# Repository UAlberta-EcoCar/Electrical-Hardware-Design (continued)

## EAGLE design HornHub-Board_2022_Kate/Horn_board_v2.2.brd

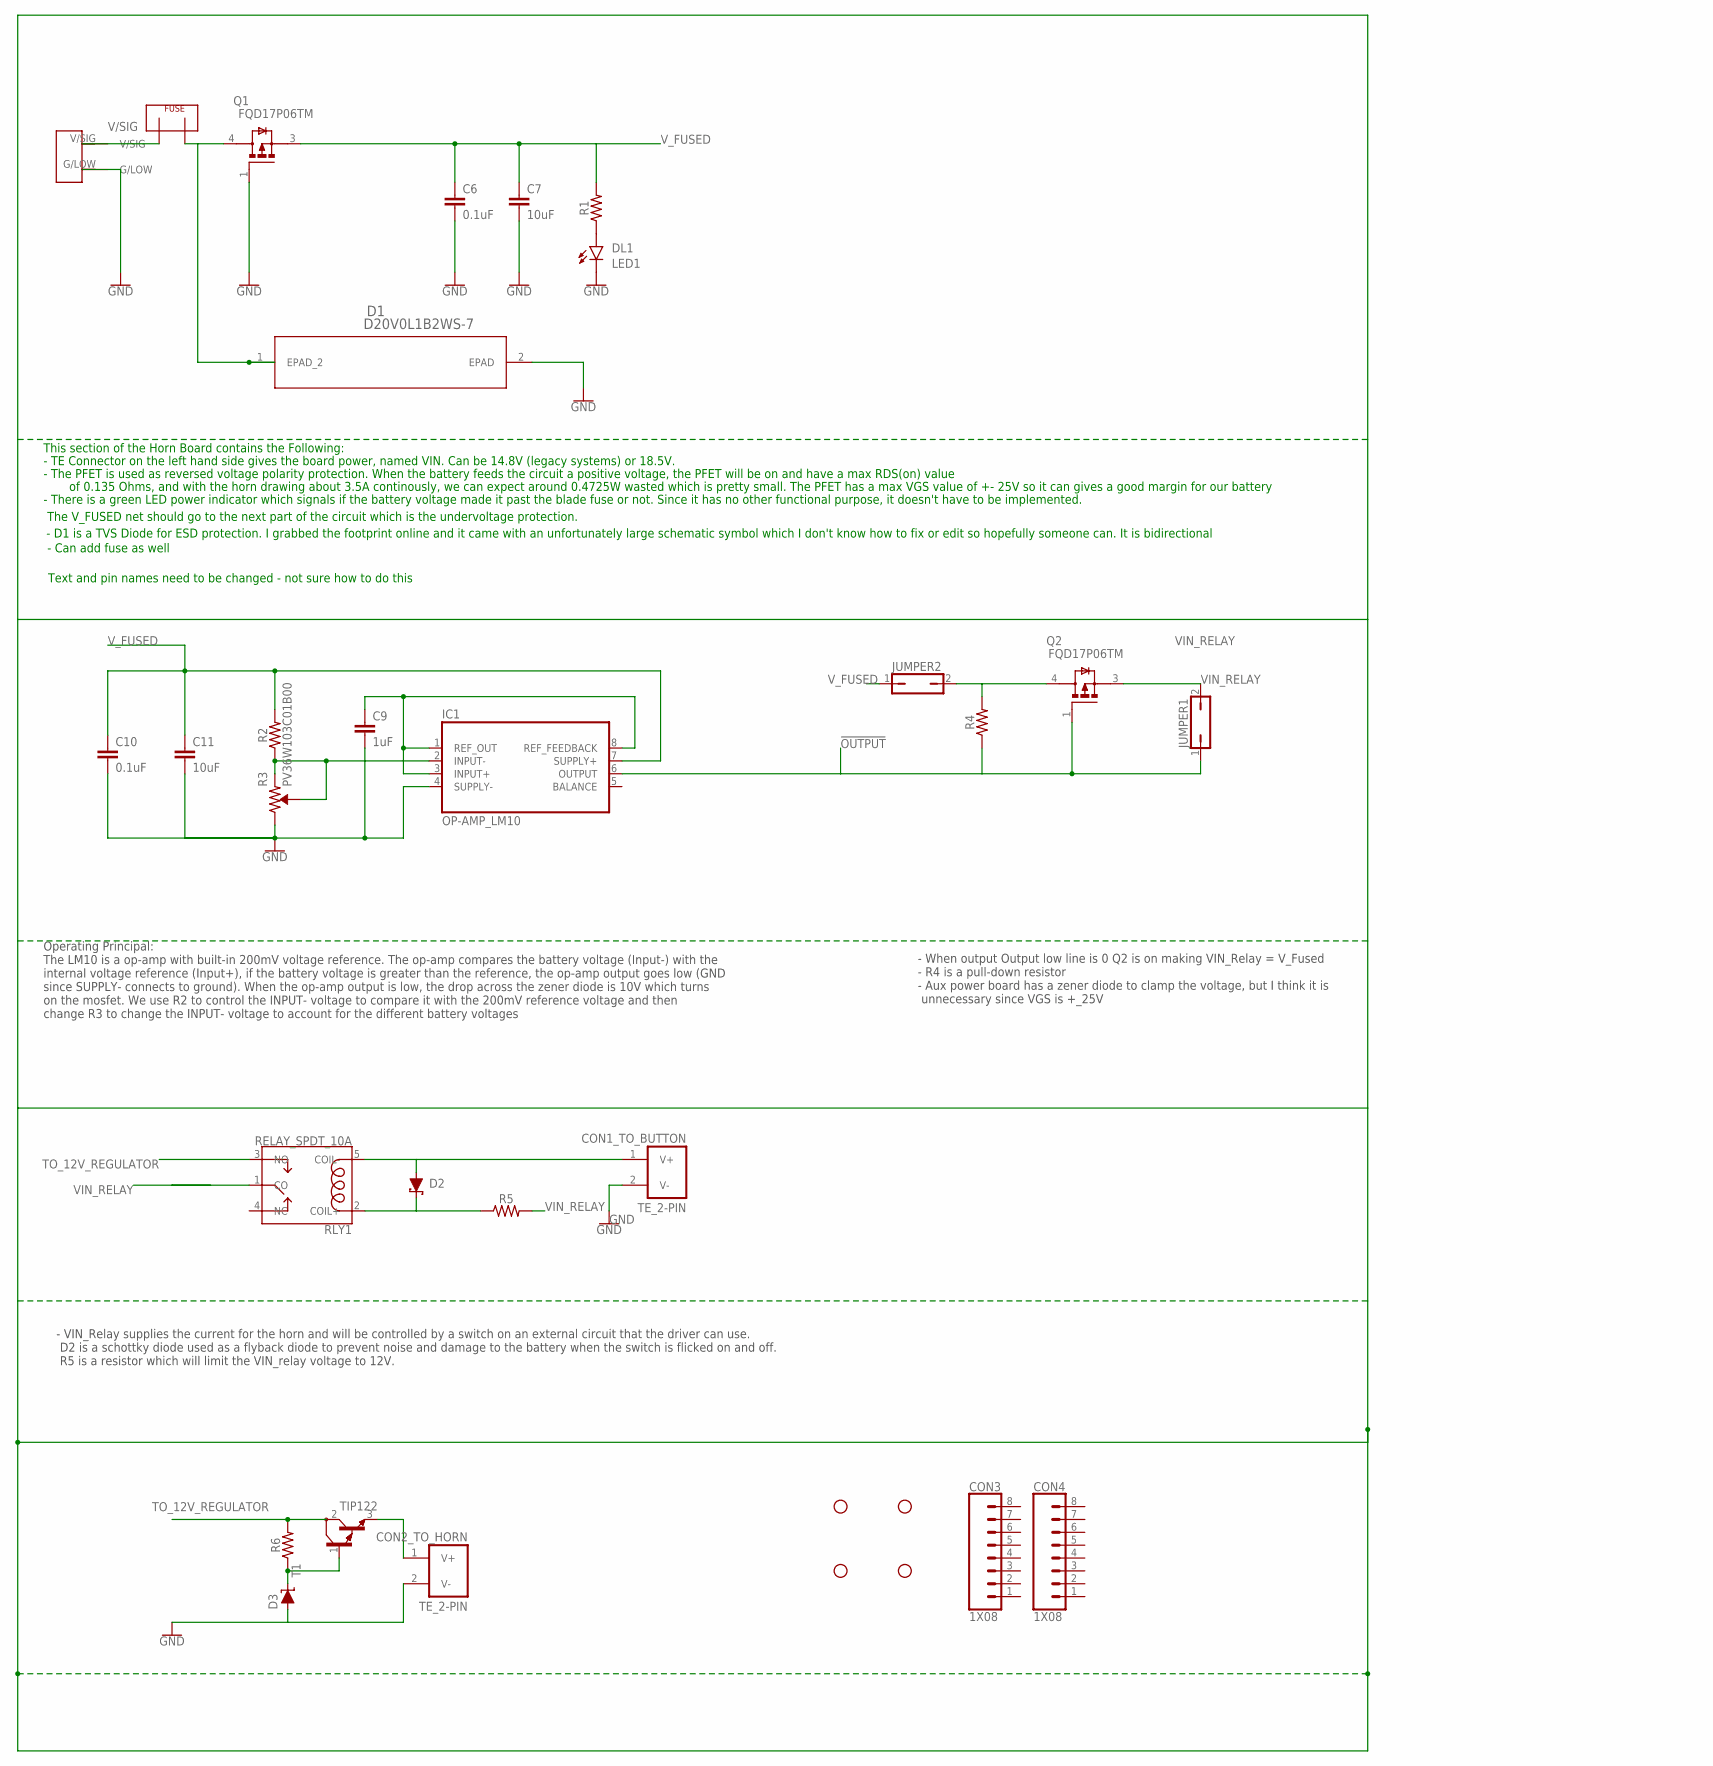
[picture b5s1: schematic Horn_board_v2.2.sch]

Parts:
C6, C10: 0.1uF; 1210
C7, C11: 10uF; 1210
C9: 1uF; 1210
CON1_TO_BUTTON, CON2_TO_HORN: TE_2-PIN
CON3, CON4: 1X08
D1: D20V0L1B2WS-7; SOD323_DIO
D2: DIODE_SCHOTTKY_DO-214AA; DO214AA
D3: DIODE_TVS_DO-214AA; DO214AA
F1: FUSEMINI-BLADE; MINI-BLADE-FUSE
H1, H2, H3, H4: STAND-OFF
IC1: OP-AMP_LM10; DIP08
JUMPER1, JUMPER2: JP1Q; JP1
LED1: DL1; 0805_LED
PWR: 2_PIN_TECONNECTOR; 2_PIN_CONNECT
Q1, Q2: FQD17P06TM; DPAK229P990X239-4N
R1, R2, R4, R5, R6: RESISTOR_1210; 1210
R3: PV36W103C01B00; TRIMPOT
RLY1: RELAY_SPDT_10A
T1: TIP122; TO220

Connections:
!OUTPUT: IC1.6 (OUTPUT), JUMPER1.1, Q2.1 (G), R4.1
GND: C6.2, C7.2, C10.2, C11.2, CON1_TO_BUTTON.2 (V-), CON2_TO_HORN.2 (V-), D1.2 (EPAD), D3.A, LED1.2 (C), PWR.G/LOW, Q1.1 (G), R3.3 (CW)
unnamed: C9.2, IC1.4 (SUPPLY-)
unnamed: LED1.1 (A), R1.1
unnamed: IC1.2 (INPUT-), R2.1, R3.1 (CCW), R3.2 (WIPER)
unnamed: C9.1, IC1.1 (REF_OUT), IC1.3 (INPUT+), IC1.8 (REF_FEEDBACK)
unnamed: JUMPER2.2, Q2.4 (D), R4.2
unnamed: D2.C, R5.1, RLY1.2 (COIL+)
unnamed: CON1_TO_BUTTON.1 (V+), D2.A, RLY1.5 (COIL-)
unnamed: D3.C, R6.1, T1.1 (B)
unnamed: CON2_TO_HORN.1 (V+), T1.3 (E)
TO_12V_REGULATOR: R6.2, RLY1.3 (NO), T1.2 (C)
V/SIG: F1.OUT, PWR.V/SIG
VIN: D1.1 (EPAD_2), F1.IN, Q1.4 (D)
VIN_RELAY: JUMPER1.2, Q2.3 (S), R5.2
V_FUSED: C6.1, C7.1, C10.1, C11.1, IC1.7 (SUPPLY+), JUMPER2.1, Q1.3 (S), R1.2, R2.2

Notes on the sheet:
This section of the Horn Board contains the Following:
- TE Connector on the left hand side gives the board power, named VIN. Can be 14.8V (legacy systems) or 18.5V.
- The PFET is used as reversed voltage polarity protection. When the battery feeds the circuit a positive voltage, the PFET will be on and have a max RDS(on) value
- There is a green LED power indicator which signals if the battery voltage made it past the blade fuse or not. Since it has no other functional purpose, it doesn't have to be implemented.
of 0.135 Ohms, and with the horn drawing about 3.5A continously, we can expect around 0.4725W wasted which is pretty small. The PFET has a max VGS value of +- 25V so it can gives a good margin for our battery
The V_FUSED net should go to the next part of the circuit which is the undervoltage protection.
- D1 is a TVS Diode for ESD protection. I grabbed the footprint online and it came with an unfortunately large schematic symbol which I don't know how to fix or edit so hopefully someone can. It is bidirectional
Text and pin names need to be changed - not sure how to do this
- Can add fuse as well
Operating Principal: The LM10 is a op-amp with built-in 200mV voltage reference. The op-amp compares the battery voltage (Input-) with the internal voltage reference (Input+), if the battery voltage is greater than the reference, the op-amp output goes low (GND since SUPPLY- connects to ground). Wh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
- When output Output low line is 0 Q2 is on making VIN_Relay = V_Fused - R4 is a pull-down resistor - Aux power board has a zener diode to clamp the voltage, but I think it is unnecessary since VGS is +_25V
- VIN_Relay supplies the current for the horn and will be controlled by a switch on an external circuit that the driver can use. D2 is a schottky diode used as a flyback diode to prevent noise and damage to the battery when the switch is flicked on and off. R5 is a resistor which will limit the VIN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

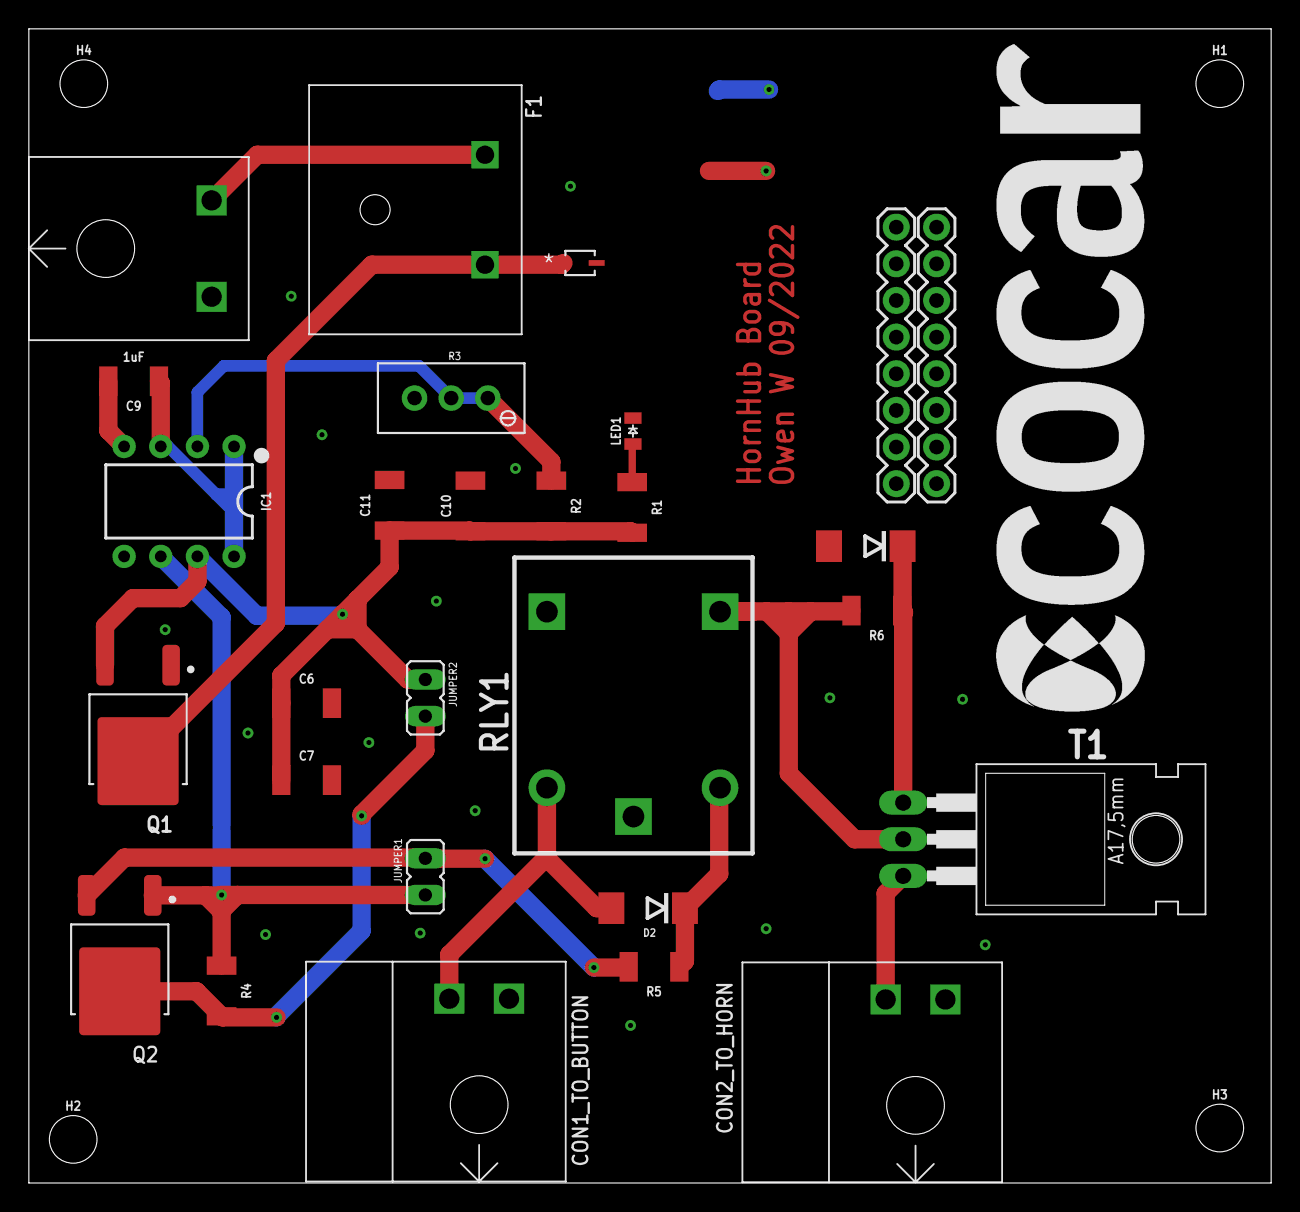
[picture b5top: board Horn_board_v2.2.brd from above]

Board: 2 copper layers, 86.1 x 80.0 mm, 33 parts (0 on the bottom side), 16 nets.

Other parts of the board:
U$1: ECOCAR_LOGO_2018

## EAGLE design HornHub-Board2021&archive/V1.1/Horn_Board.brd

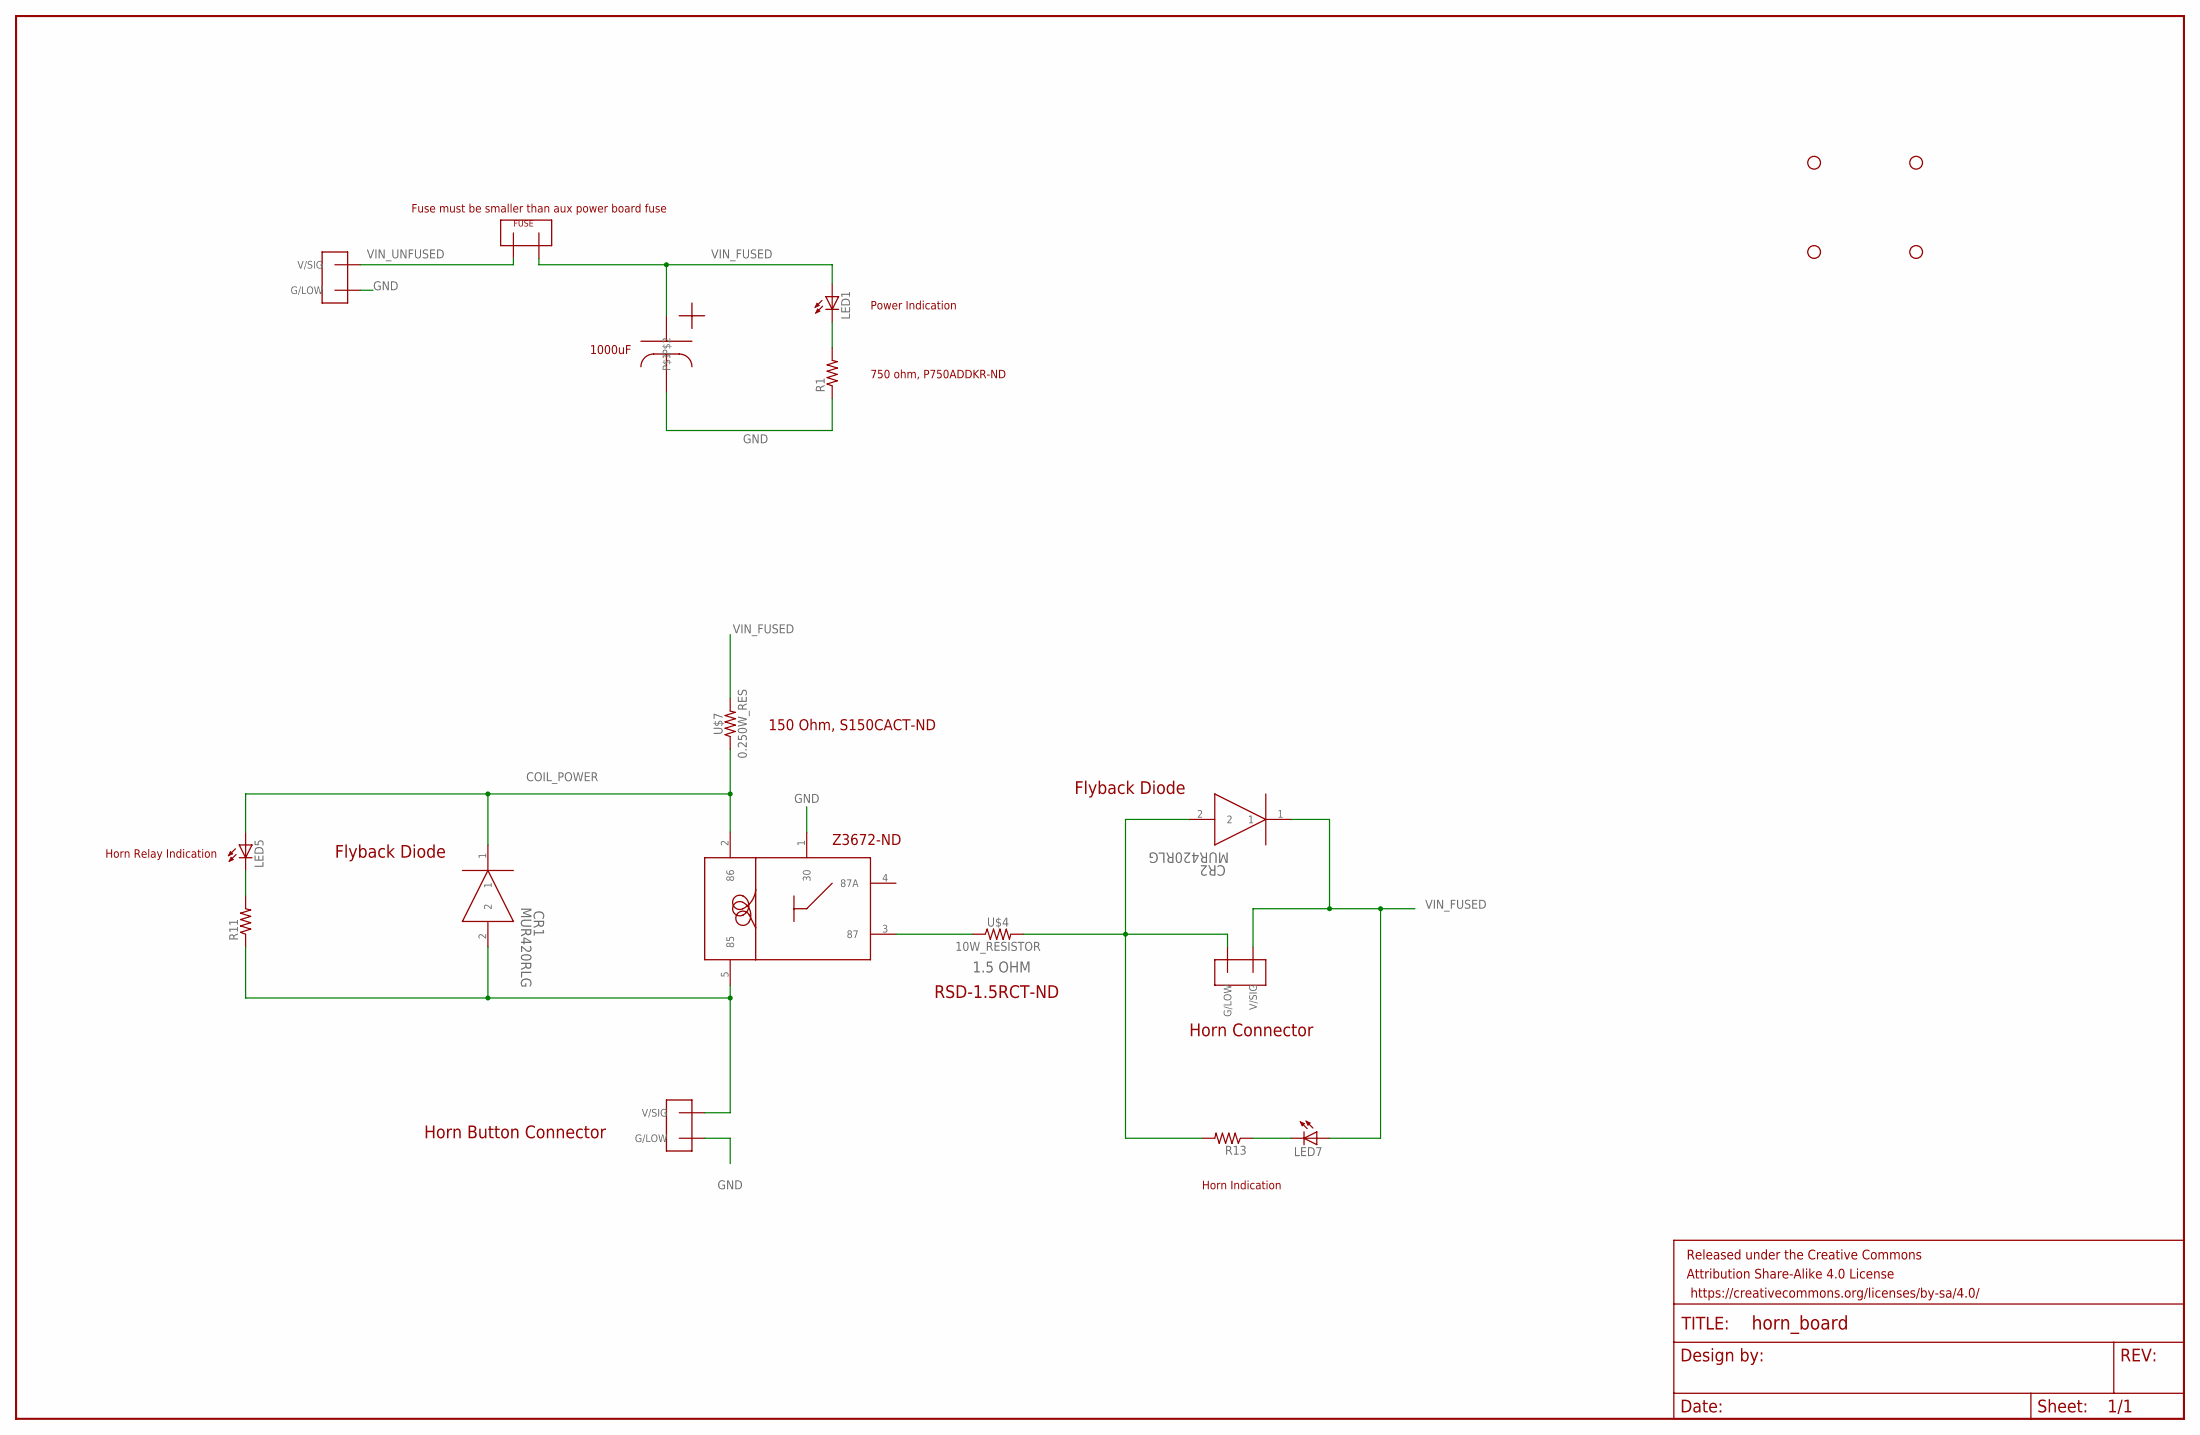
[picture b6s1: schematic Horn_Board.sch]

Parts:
CR1, CR2: MUR420RLG; DO-201AD
FRAME1: FRAME-LEDGER; CREATIVE_COMMONS
H1, H2, H3, H4: STAND-OFF
LED1, LED5, LED7: LEDCHIP-LED0805; CHIP-LED0805
R1, R11, R13: R-US_M0805; M0805
U$1, U$17, U$18: TE770966; 2X1-MATE-N-LOCK
U$2: FUSEMINI-BLADE; MINI-BLADE-FUSE
U$3: OMRON_G5LE-1
U$4: 10W_RESISTOR
U$7: 0.250W_RES; AXIAL-0.3
U$22: CAPESK108M025AH4EA; ESK108M025AH4EA

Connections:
COIL_POWER: CR1.1, LED5.A, U$3.2 (86), U$7.P$1 (1)
GND: R1.1, U$1.CIRCUIT2 (G/LOW), U$3.1 (30), U$17.CIRCUIT2 (G/LOW), U$22.P$2
HORN-: CR2.2, R13.2, U$4.P$2 (2), U$18.CIRCUIT2 (G/LOW)
HORN_BUTTON: CR1.2, R11.1, U$3.5 (85), U$17.CIRCUIT1 (V/SIG)
unnamed: U$3.3 (87), U$4.P$1 (1)
unnamed: LED1.C, R1.2
unnamed: LED5.C, R11.2
unnamed: LED7.C, R13.1
VIN_FUSED: CR2.1, LED1.A, LED7.A, U$2.OUT, U$7.P$2 (2), U$18.CIRCUIT1 (V/SIG), U$22.P$1
VIN_UNFUSED: U$1.CIRCUIT1 (V/SIG), U$2.IN

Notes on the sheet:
1.5 OHM
Horn Connector
Flyback Diode
Horn Button Connector
Z3672-ND
150 Ohm, S150CACT-ND
Horn Relay Indication
Horn Indication
Power Indication
750 ohm, P750ADDKR-ND
1000uF
Fuse must be smaller than aux power board fuse
RSD-1.5RCT-ND

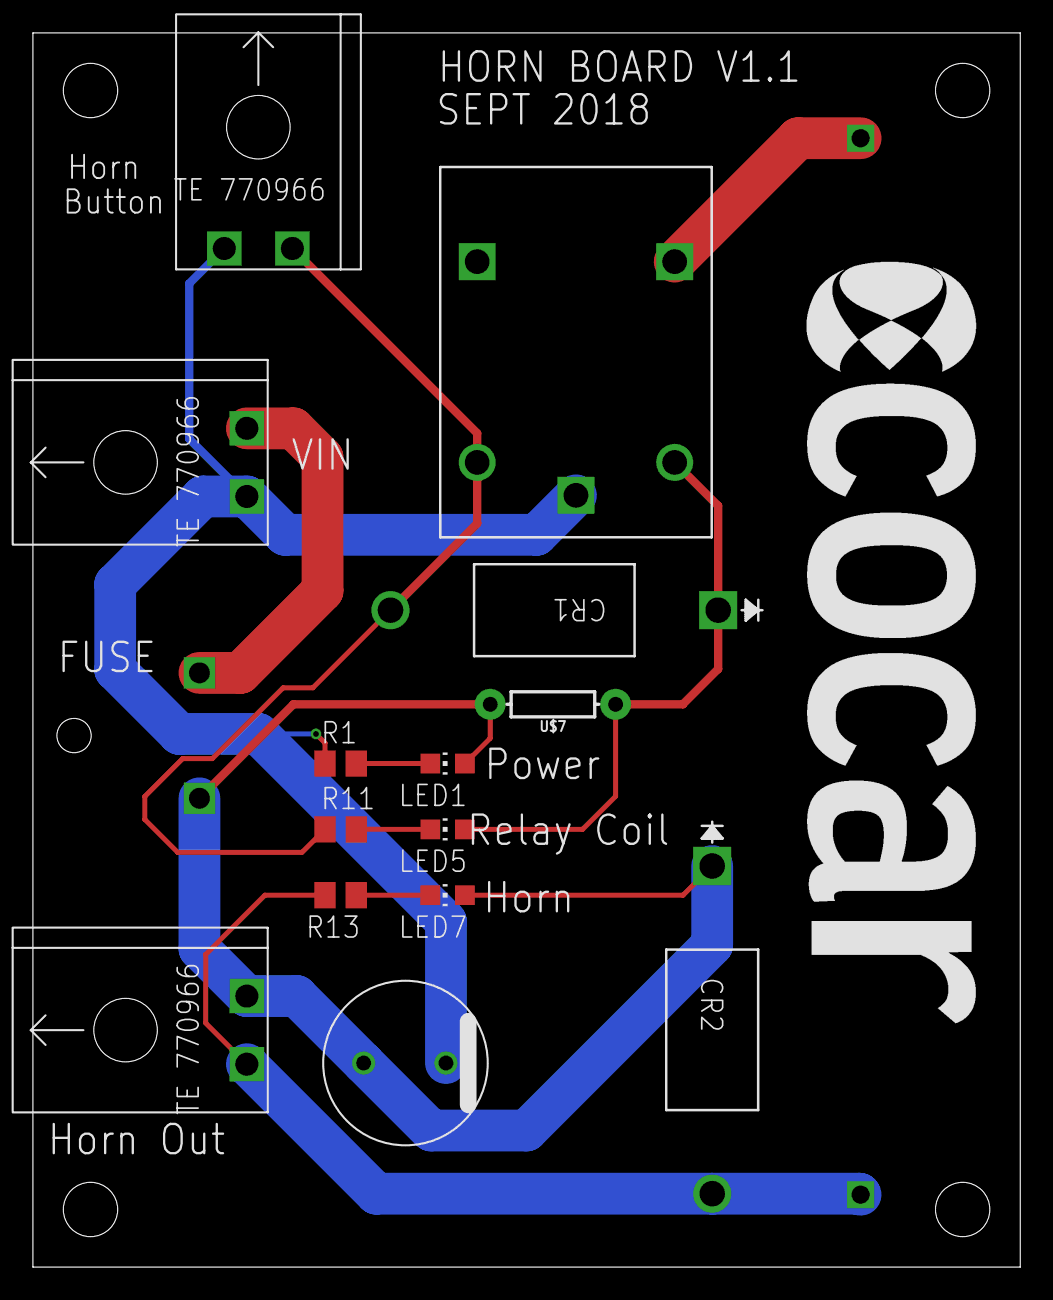
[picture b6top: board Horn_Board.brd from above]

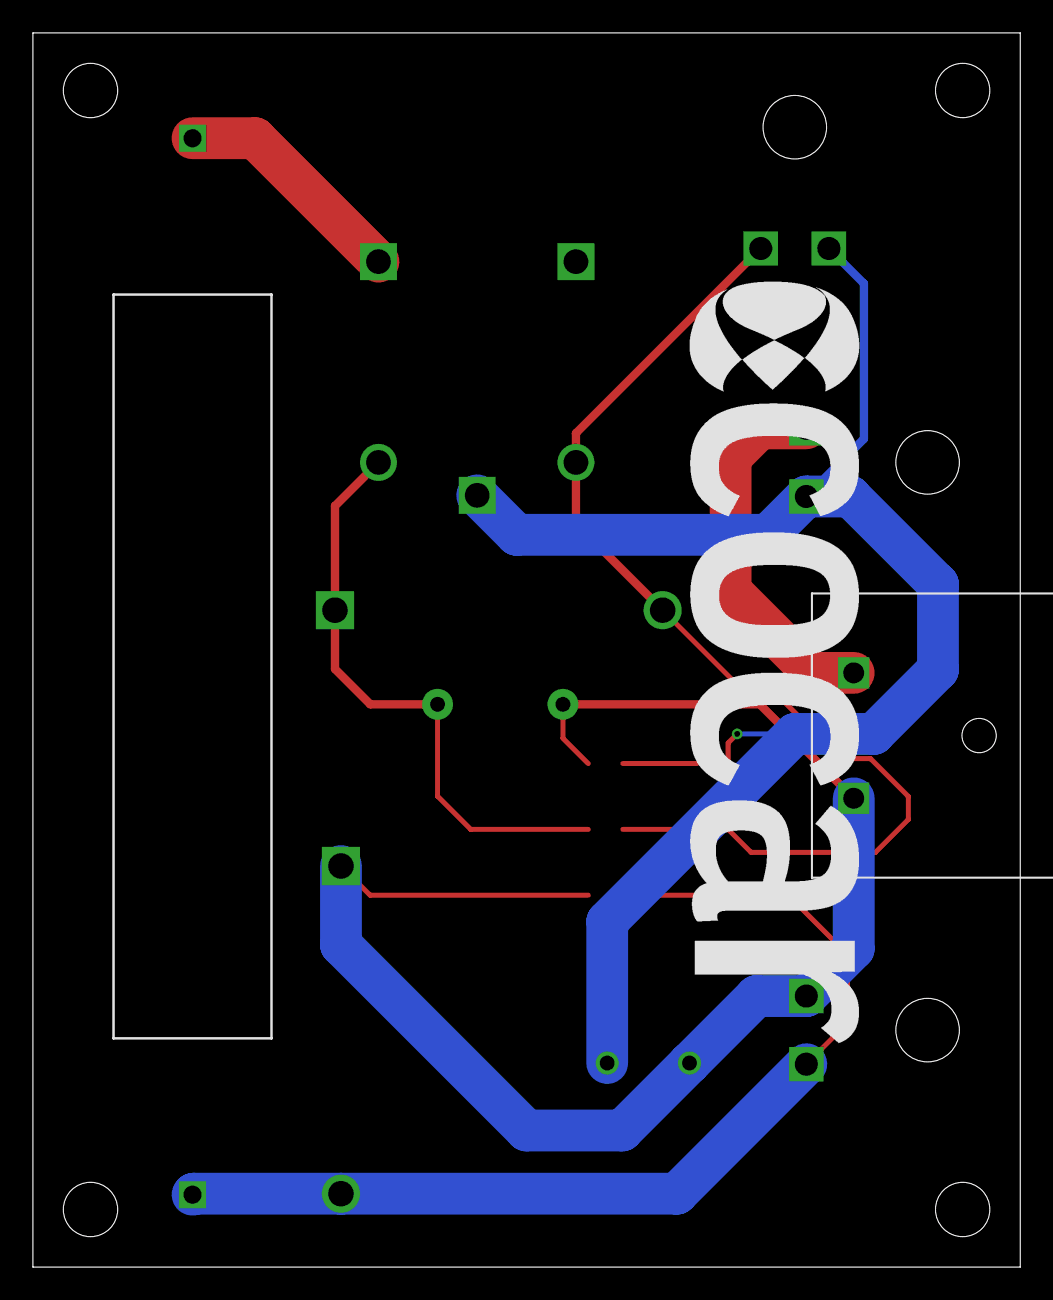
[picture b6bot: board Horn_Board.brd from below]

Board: 2 copper layers, 60.0 x 75.0 mm, 23 parts (3 on the bottom side), 10 nets.

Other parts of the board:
U$5, U$14: ECOCAR_LOGO_2018

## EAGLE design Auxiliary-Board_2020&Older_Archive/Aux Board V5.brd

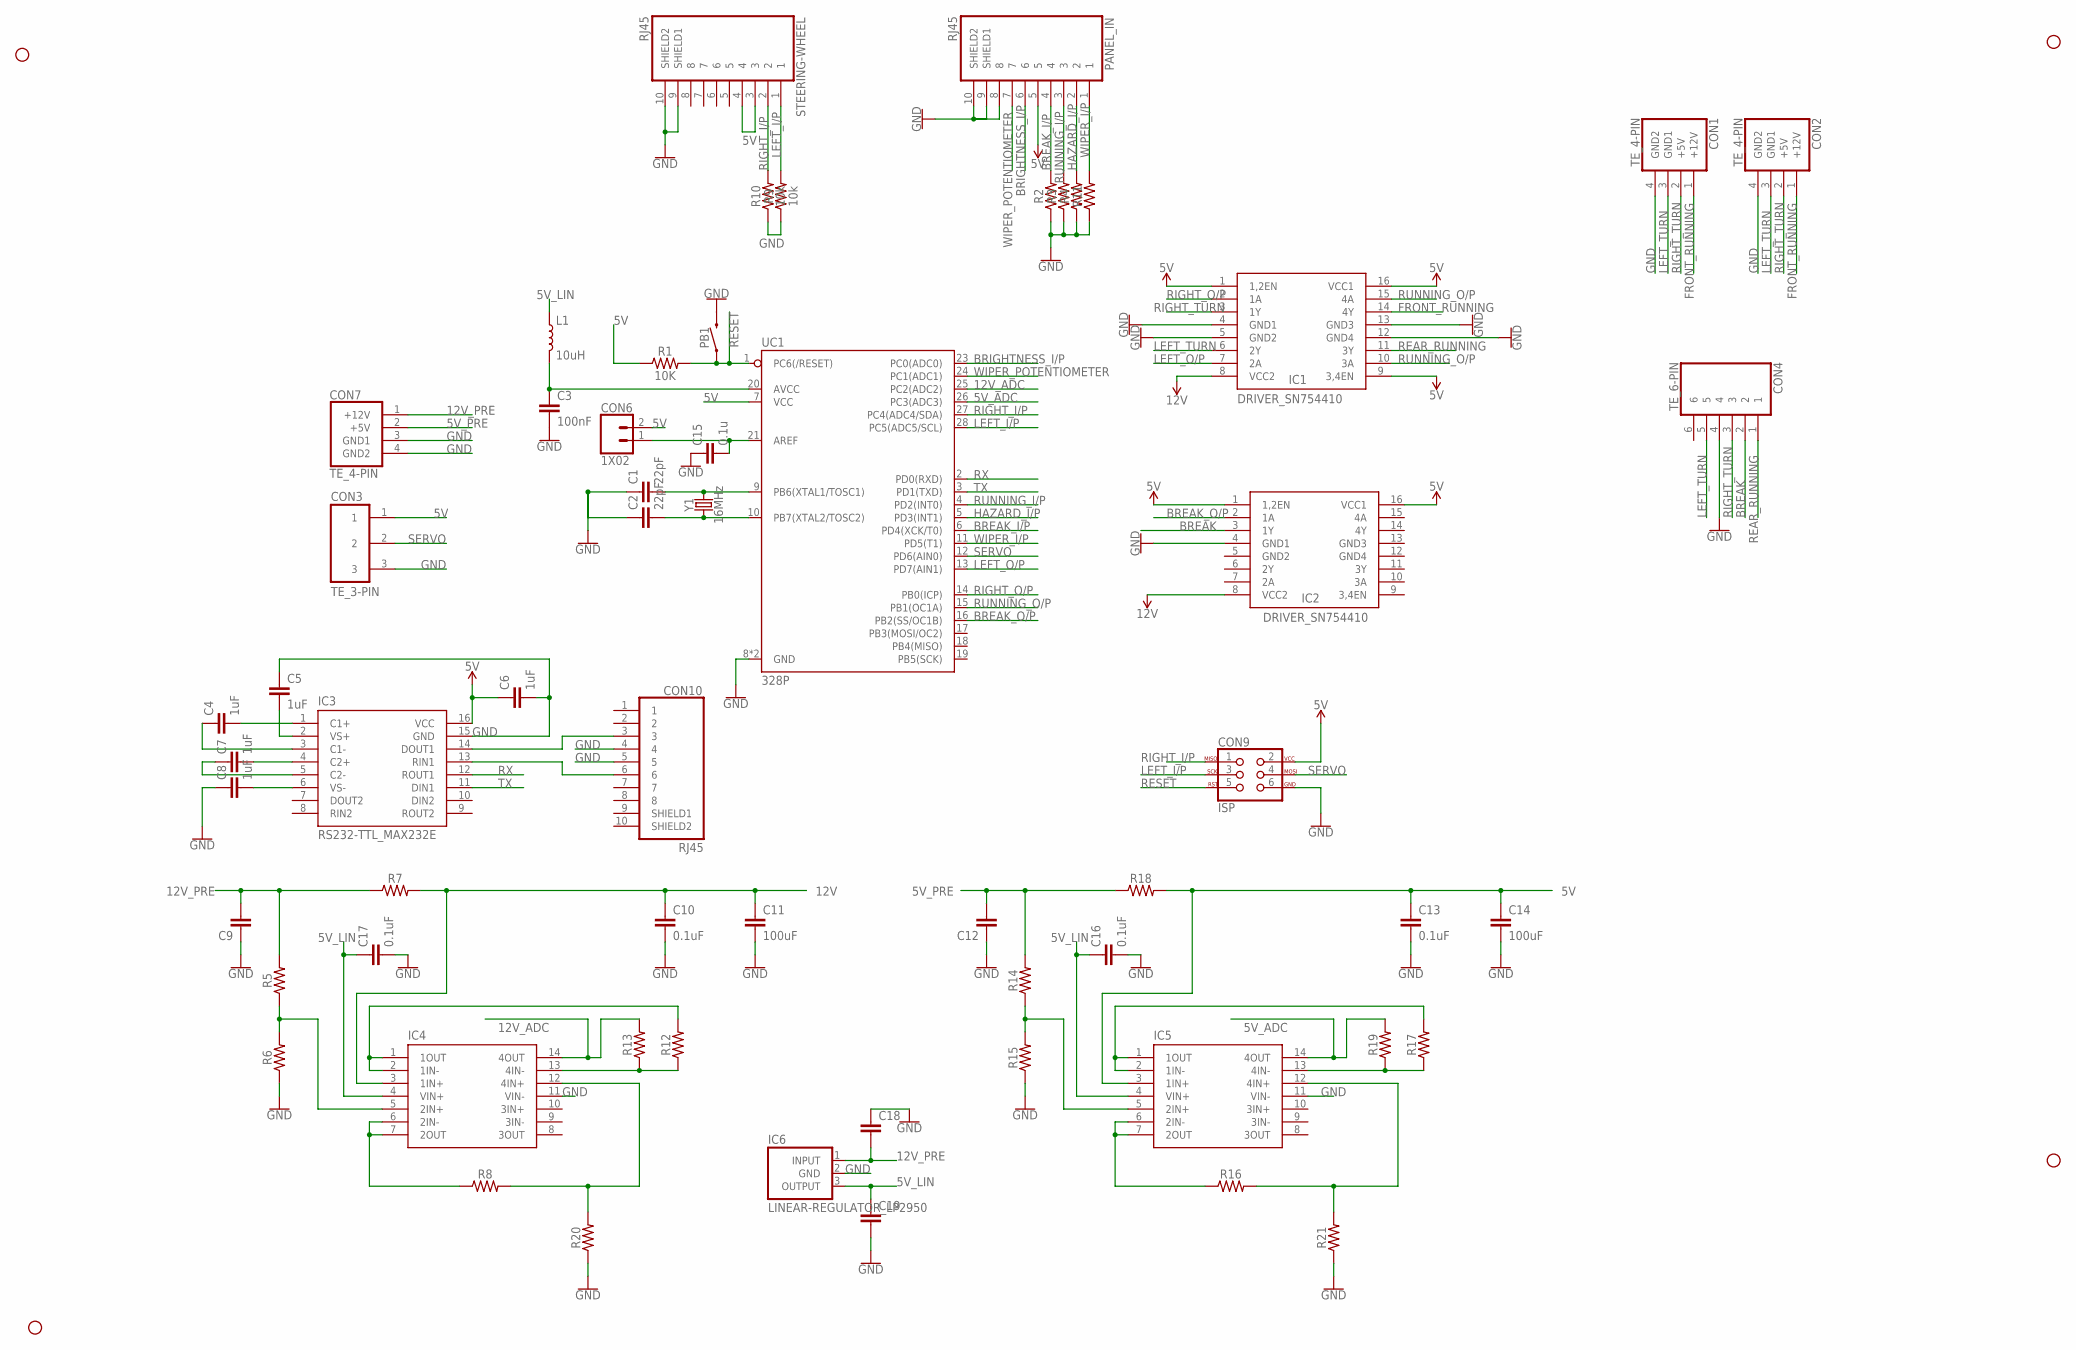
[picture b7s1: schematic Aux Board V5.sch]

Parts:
C1, C2: 22pF; 0805
C3: 100nF; 0805
C4, C5, C6, C7, C8: 1uF; 0805
C9, C12, C18, C19: CAPACITOR_0805; 0805
C10, C13, C16, C17: 0.1uF; 0805
C11, C14: 100uF; 0805
C15: 0.1u; 0805
CON1, CON2, CON7: TE_4-PIN
CON3: TE_3-PIN
CON4: TE_6-PIN
CON6: 1X02
CON9: ISP; ISP_CONNECTOR
CON10: RJ45
H1, H2, H3, H4: STAND-OFF
IC1, IC2: DRIVER_SN754410; DIP16
IC3: RS232-TTL_MAX232E; DIP16
IC4, IC5: OP-AMP_QUAD; DIP14
IC6: LINEAR-REGULATOR_LP2950; TO92
L1: 10uH; 0805
PANEL_IN: RJ45
PB1: PUSHBUTTON
R1: 10K; 0805
R2, R3, R4, R5, R6, R8, R11, R12, R13, R14, R15, R16, R17, R19, R20, R21: RESISTOR_0805; 0805
R7, R18: RESISTOR_1210; 1210
R9, R10: 10k; 0805
STEERING-WHEEL: RJ45
UC1: 328P; DIP28
Y1: 16MHz; HC49US

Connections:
5V: C6.1, C13.1, C14.1, C15.2, CON3.1, CON6.1, CON6.2, CON9.2, IC1.1 (1,2EN), IC1.9 (3,4EN), IC1.16 (VCC1), IC2.1 (1,2EN), IC2.16 (VCC1), IC3.16 (VCC), IC5.3 (1IN+), PANEL_IN.5, R1.1, R18.2, STEERING-WHEEL.3, STEERING-WHEEL.4, UC1.7 (VCC), UC1.21 (AREF)
5V_ADC: IC5.14 (4OUT), R19.2, UC1.26 (PC3(ADC3))
5V_LIN: C16.1, C17.1, C19.1, IC4.4 (VIN+), IC5.4 (VIN+), IC6.3 (OUTPUT), L1.1
5V_PRE: C12.2, CON7.2 (+5V), R14.2, R18.1
12V: C10.1, C11.1, IC1.8 (VCC2), IC2.8 (VCC2), IC4.3 (1IN+), R7.2
12V_ADC: IC4.14 (4OUT), R13.2, UC1.25 (PC2(ADC2))
12V_PRE: C9.2, C18.2, CON7.1 (+12V), IC6.1 (INPUT), R5.2, R7.1
BREAK: CON4.2, IC2.3 (1Y)
BREAK_I/P: PANEL_IN.4, R2.2, UC1.6 (PD4(XCK/T0))
BREAK_O/P: IC2.2 (1A), UC1.16 (PB2(SS/OC1B))
BRIGHTNESS_I/P: PANEL_IN.6, UC1.23 (PC0(ADC0))
FRONT_RUNNING: CON1.1 (+12V), CON2.1 (+12V), IC1.14 (4Y)
GND: C1.1, C2.1, C3.2, C5.1, C6.2, C8.1, C9.1, C10.2, C11.2, C12.1, C13.2, C14.2, C15.1, C16.2, C17.2, C18.1, C19.2, CON1.4 (GND2), CON2.4 (GND2), CON3.3, CON4.4, CON7.3 (GND1), CON7.4 (GND2), CON9.6, CON10.4, CON10.5, IC1.4 (GND1), IC1.5 (GND2), IC1.12 (GND4), IC1.13 (GND3), IC2.4 (GND1), IC3.15 (GND), IC4.11 (VIN-), IC5.11 (VIN-), IC6.2 (GND), PANEL_IN.8, PANEL_IN.9 (SHIELD1), PANEL_IN.10 (SHIELD2), PB1.3 (2), PB1.4 (2), R2.1, R3.1, R4.1, R6.1, R9.1, R10.1, R11.1, R15.1, R20.1, R21.1, STEERING-WHEEL.9 (SHIELD1), STEERING-WHEEL.10 (SHIELD2), UC1.8 (GND), UC1.22 (GND)
HAZARD_I/P: PANEL_IN.2, R4.2, UC1.5 (PD3(INT1))
LEFT_I/P: CON9.3, R9.2, STEERING-WHEEL.1, UC1.28 (PC5(ADC5/SCL))
LEFT_O/P: IC1.7 (2A), UC1.13 (PD7(AIN1))
LEFT_TURN: CON1.3 (GND1), CON2.3 (GND1), CON4.5, IC1.6 (2Y)
unnamed: C4.2, IC3.1 (C1+)
unnamed: IC4.5 (2IN+), R5.1, R6.2
unnamed: C4.1, IC3.3 (C1-)
unnamed: C5.2, IC3.2 (VS+)
unnamed: IC4.6 (2IN-), IC4.7 (2OUT), R8.1
unnamed: IC5.5 (2IN+), R14.1, R15.2
unnamed: IC4.1 (1OUT), IC4.2 (1IN-), R12.2
unnamed: C1.2, UC1.9 (PB6(XTAL1/TOSC1)), Y1.2
unnamed: C2.2, UC1.10 (PB7(XTAL2/TOSC2)), Y1.1
unnamed: C7.2, IC3.4 (C2+)
unnamed: C7.1, IC3.5 (C2-)
unnamed: C8.2, IC3.6 (VS-)
unnamed: CON10.3, IC3.14 (DOUT1)
unnamed: CON10.6, IC3.13 (RIN1)
unnamed: IC4.13 (4IN-), R12.1, R13.1
unnamed: IC5.6 (2IN-), IC5.7 (2OUT), R16.1
unnamed: IC5.1 (1OUT), IC5.2 (1IN-), R17.2
unnamed: IC5.13 (4IN-), R17.1, R19.1
unnamed: C3.1, L1.2, UC1.20 (AVCC)
unnamed: IC4.12 (4IN+), R8.2, R20.2
unnamed: IC5.12 (4IN+), R16.2, R21.2
REAR_RUNNING: CON4.1, IC1.11 (3Y)
RESET: CON9.5, PB1.1, PB1.2 (1), R1.2, UC1.1 (PC6(/RESET))
RIGHT_I/P: CON9.1, R10.2, STEERING-WHEEL.2, UC1.27 (PC4(ADC4/SDA))
RIGHT_O/P: IC1.2 (1A), UC1.14 (PB0(ICP))
RIGHT_TURN: CON1.2 (+5V), CON2.2 (+5V), CON4.3, IC1.3 (1Y)
RUNNING_I/P: PANEL_IN.3, R3.2, UC1.4 (PD2(INT0))
RUNNING_O/P: IC1.10 (3A), IC1.15 (4A), UC1.15 (PB1(OC1A))
RX: IC3.12 (ROUT1), UC1.2 (PD0(RXD))
SERVO: CON3.2, CON9.4, UC1.12 (PD6(AIN0))
TX: IC3.11 (DIN1), UC1.3 (PD1(TXD))
WIPER_I/P: PANEL_IN.1, R11.2, UC1.11 (PD5(T1))
WIPER_POTENTIOMETER: PANEL_IN.7, UC1.24 (PC1(ADC1))

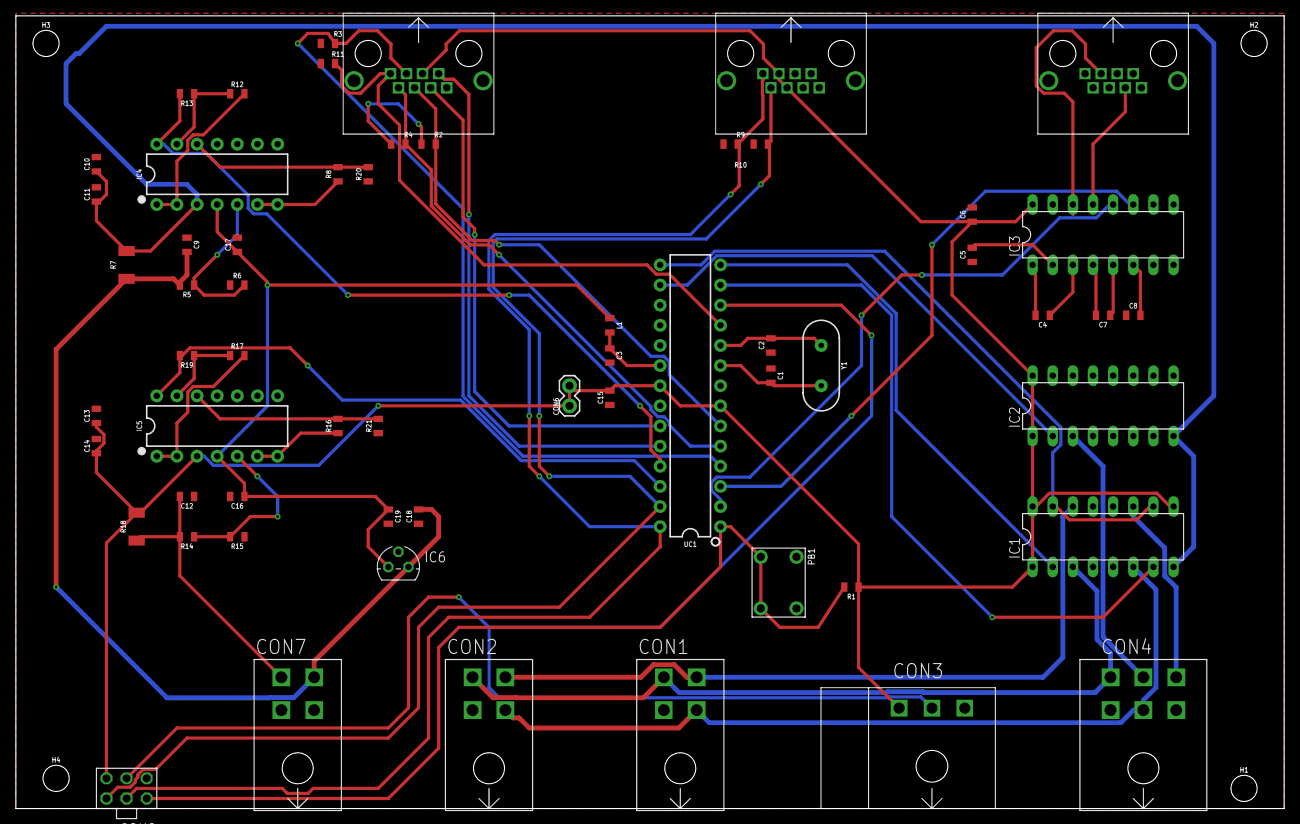
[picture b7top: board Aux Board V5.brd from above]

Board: 2 copper layers, 160.0 x 100.0 mm, 64 parts (0 on the bottom side), 50 nets.

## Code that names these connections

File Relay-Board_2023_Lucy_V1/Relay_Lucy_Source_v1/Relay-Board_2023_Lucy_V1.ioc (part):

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Mcu.Name=STM32F446R(C-E)Tx
Mcu.Package=LQFP64
Mcu.UserName=STM32F446RETx
PA11.Mode=Device_Only
PA11.Signal=USB_OTG_FS_DM
PA12.Mode=Device_Only
PA12.Signal=USB_OTG_FS_DP
PA13.Mode=Serial_Wire
PA13.Signal=SYS_JTMS-SWDIO
PA14.Mode=Serial_Wire
PA14.Signal=SYS_JTCK-SWCLK
PA4.GPIOParameters=GPIO_Label
PA4.GPIO_Label=FC_VOLT
PA4.Signal=ADCx_IN4
PA5.GPIOParameters=GPIO_Label
PA5.GPIO_Label=MOTOR_CURR
PA5.Signal=ADCx_IN5
PA6.GPIOParameters=GPIO_Label
PA6.GPIO_Label=CAP_VOLT
PA6.Signal=ADCx_IN6
PA7.GPIOParameters=GPIO_Label
PA7.GPIO_Label=CAP_CURR
PA7.Signal=ADCx_IN7
PA8.Mode=Clock-out-1
PA8.Signal=RCC_MCO_1
PB0.GPIOParameters=GPIO_Label
PB0.GPIO_Label=DSCHRGE_RELAY
PB0.Signal=GPIO_Output
PB1.GPIOParameters=GPIO_Label
PB1.GPIO_Label=RES_RELAY
PB1.Signal=GPIO_Output
PB10.GPIOParameters=GPIO_Label
PB10.GPIO_Label=MTR_RELAY
PB10.Signal=GPIO_Output
PB12.GPIOParameters=GPIO_Label
PB12.GPIO_Label=DSCHRGE_LED
PB12.Signal=GPIO_Output
PB13.GPIOParameters=GPIO_Label
PB13.GPIO_Label=RES_LED
PB13.Signal=GPIO_Output
PB14.GPIOParameters=GPIO_Label
PB14.GPIO_Label=MTR_LED
PB14.Signal=GPIO_Output
PB15.GPIOParameters=GPIO_Label
PB15.GPIO_Label=CAP_LED
PB15.Signal=GPIO_Output
PB2.GPIOParameters=GPIO_Label
PB2.GPIO_Label=CAP_RELAY
PB2.Signal=GPIO_Output
PB7.GPIOParameters=GPIO_Label
PB7.GPIO_Label=CAN_STBY
PB7.Signal=GPIO_Output
PB8.Mode=CAN_Activate
PB8.Signal=CAN1_RX
PB9.Mode=CAN_Activate
PB9.Signal=CAN1_TX
PC4.GPIOParameters=GPIO_Label
PC4.GPIO_Label=MTR_VOLT
PC4.Signal=ADCx_IN14
PC5.GPIOParameters=GPIO_Label
PC5.GPIO_Label=FC_CURR
PC5.Signal=ADCx_IN15
PC9.Mode=Clock-out-2
PC9.Signal=RCC_MCO_2
PH0-OSC_IN.Mode=HSE-External-Clock-Source
PH0-OSC_IN.Signal=RCC_OSC_IN
PH1-OSC_OUT.Mode=HSE-External-Clock-Source
PH1-OSC_OUT.Signal=RCC_OSC_OUT
RCC.HSE_VALUE=8000000
RCC.SYSCLKFreq_VALUE=180000000
RCC.SYSCLKSource=RCC_SYSCLKSOURCE_PLLCLK
board=custom

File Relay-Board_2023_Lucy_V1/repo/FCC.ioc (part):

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Mcu.Name=STM32F722R(C-E)Tx
Mcu.Package=LQFP64
Mcu.UserName=STM32F722RETx
PA0-WKUP.Signal=ADCx_IN0
PA1.Signal=ADCx_IN1
PA11.Mode=Device_Only
PA11.Signal=USB_OTG_FS_DM
PA12.Mode=Device_Only
PA12.Signal=USB_OTG_FS_DP
PA13.Mode=Serial_Wire
PA13.Signal=SYS_JTMS-SWDIO
PA14.Mode=Serial_Wire
PA14.Signal=SYS_JTCK-SWCLK
PA2.Signal=ADCx_IN2
PA3.Signal=ADCx_IN3
PA4.Signal=ADCx_IN4
PA5.GPIOParameters=GPIO_PuPd,GPIO_Label
PA5.GPIO_Label=DISCHARGE_RELAY
PA5.GPIO_PuPd=GPIO_PULLDOWN
PA5.Signal=GPIO_Output
PA6.GPIOParameters=GPIO_PuPd,GPIO_Label
PA6.GPIO_Label=RES_RELAY
PA6.GPIO_PuPd=GPIO_PULLDOWN
PA6.Signal=GPIO_Output
PA7.GPIOParameters=GPIO_PuPd,GPIO_Label
PA7.GPIO_Label=MTR_RELAY
PA7.GPIO_PuPd=GPIO_PULLDOWN
PA7.Signal=GPIO_Output
PA8.GPIOParameters=GPIO_PuPd,GPIO_Label
PA8.GPIO_Label=CAP_RELAY
PA8.GPIO_PuPd=GPIO_PULLDOWN
PA8.Signal=GPIO_Output
PB6.Mode=I2C
PB6.Signal=I2C1_SCL
PB7.Mode=I2C
PB7.Signal=I2C1_SDA
PB8.Mode=CAN_Activate
PB8.Signal=CAN1_RX
PB9.Mode=CAN_Activate
PB9.Signal=CAN1_TX
PC13.GPIOParameters=GPIO_PuPd,GPIO_Label
PC13.GPIO_Label=CAN_STBY
PC13.GPIO_PuPd=GPIO_PULLDOWN
PC13.Signal=GPIO_Output
PC3.Signal=ADCx_IN13
PH0-OSC_IN.Mode=HSE-External-Clock-Source
PH0-OSC_IN.Signal=RCC_OSC_IN
PH1-OSC_OUT.Mode=HSE-External-Clock-Source
PH1-OSC_OUT.Signal=RCC_OSC_OUT
RCC.HSE_VALUE=8000000
RCC.SYSCLKFreq_VALUE=200000000
RCC.SYSCLKSource=RCC_SYSCLKSOURCE_PLLCLK
board=custom
